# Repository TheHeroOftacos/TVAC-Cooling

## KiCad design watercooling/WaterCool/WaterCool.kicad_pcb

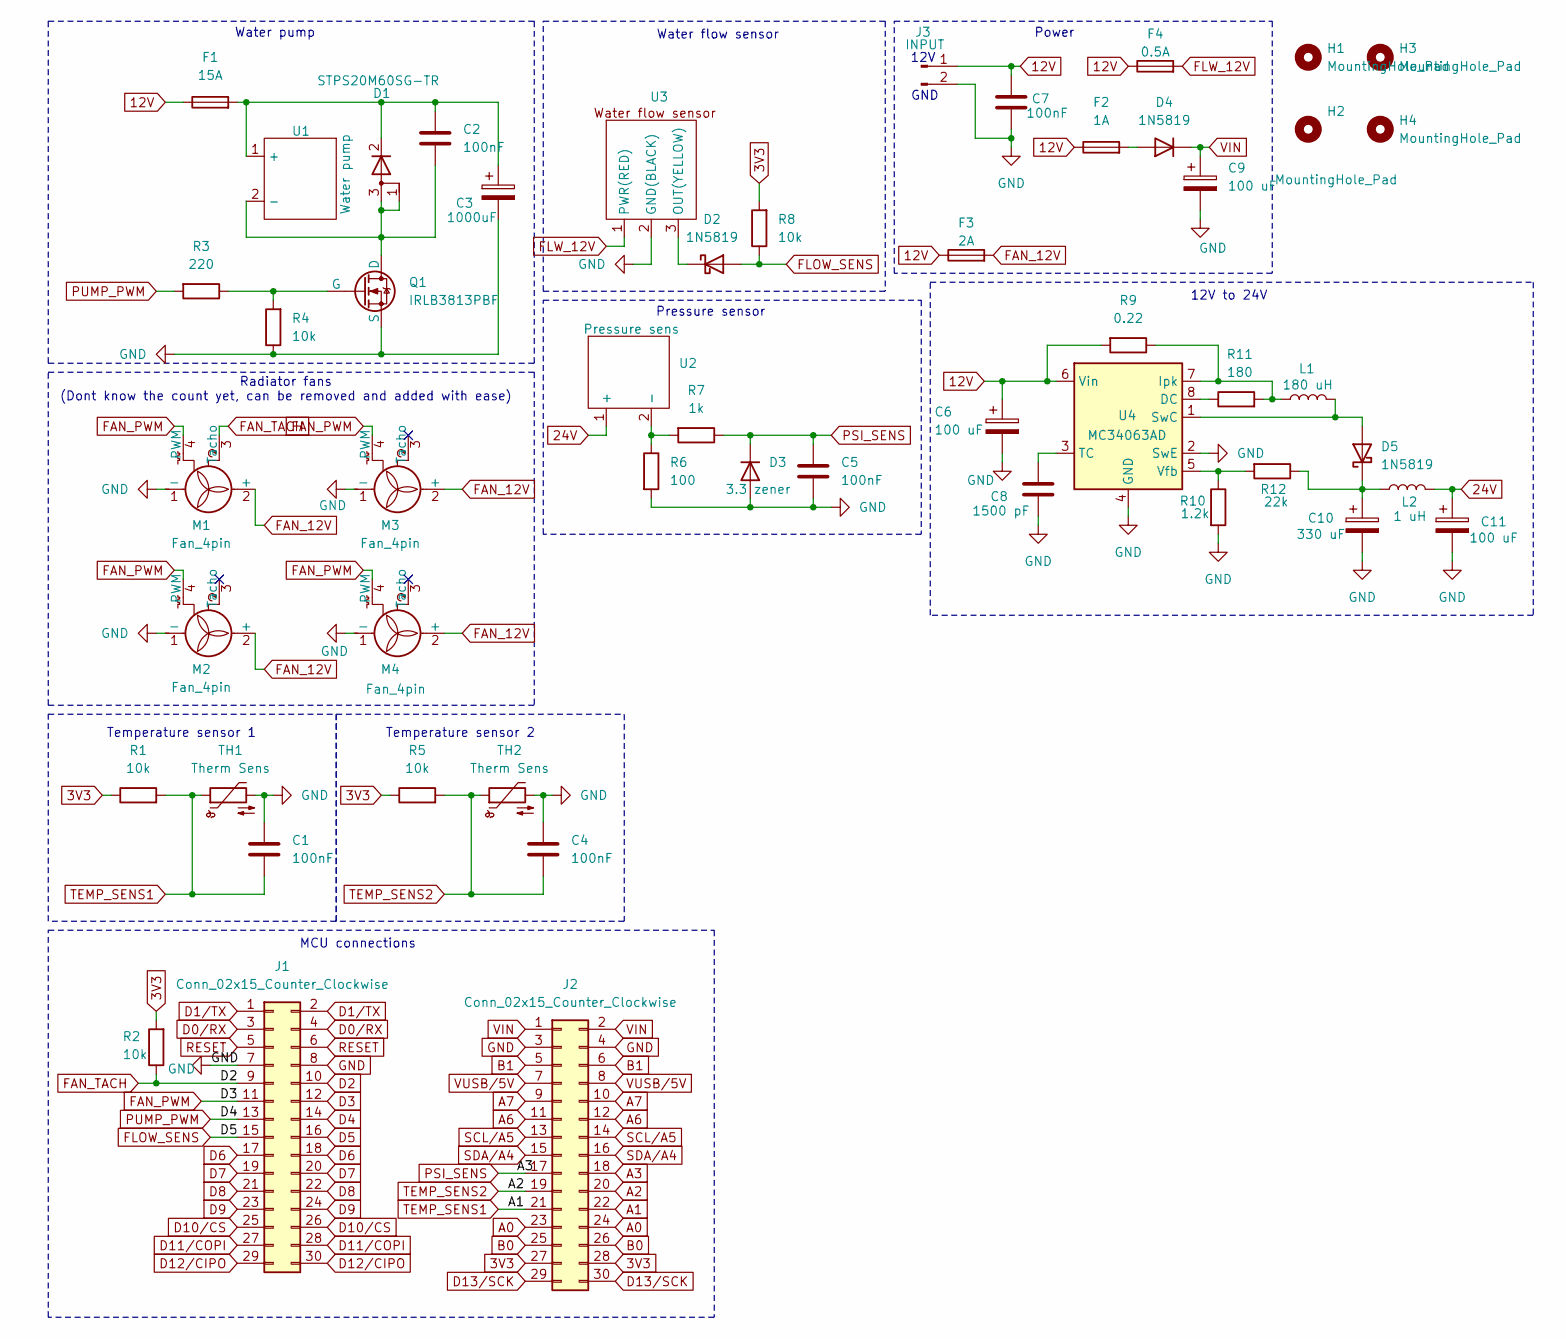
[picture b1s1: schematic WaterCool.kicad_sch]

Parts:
C1, C2, C4, C5, C7: 100nF; C_1210_3225Metric_Pad1.33x2.70mm_HandSolder
C3: 1000uF; CP_Elec_10x10.5
C6, C9, C11: 100 uF; CP_Elec_10x10.5
C8: 1500 pF; C_0805_2012Metric_Pad1.18x1.45mm_HandSolder
C10: 330 uF; CP_Elec_10x10.5
D1: STPS20M60SG-TR; TO-263-2
D2, D4, D5: 1N5819; D_SOD-123
D3: 3.3 zener; D_SOD-123
F1: 15A; Fuse_2512_6332Metric_Pad1.52x3.35mm_HandSolder
F2: 1A; Fuse_0805_2012Metric_Pad1.15x1.40mm_HandSolder
F3: 2A; Fuse_0805_2012Metric_Pad1.15x1.40mm_HandSolder
F4: 0.5A; Fuse_0805_2012Metric_Pad1.15x1.40mm_HandSolder
H1, H2, H3, H4: MountingHole_Pad; MountingHole_3.2mm_M3
J1, J2: Conn_02x15_Counter_Clockwise; PinSocket_2x15_P2.54mm_Vertical
J3: INPUT; AMASS_XT60-M_1x02_P7.20mm_Vertical
L1: 180 uH; L_Coilcraft_MSS1048-XXX
L2: 1 uH; L_Vishay_IHLP-1212
M1, M2, M3, M4: Fan_4pin; PinHeader_1x04_P2.54mm_Vertical
Q1: IRLB3813PBF; TO-220-3_Horizontal_TabDown
R1, R2, R4, R5, R8: 10k; R_0805_2012Metric_Pad1.20x1.40mm_HandSolder
R3: 220; R_0805_2012Metric_Pad1.20x1.40mm_HandSolder
R6: 100; R_0805_2012Metric_Pad1.20x1.40mm_HandSolder
R7: 1k; R_0805_2012Metric_Pad1.20x1.40mm_HandSolder
R9: 0.22; R_0805_2012Metric_Pad1.20x1.40mm_HandSolder
R10: 1.2k; R_0805_2012Metric_Pad1.20x1.40mm_HandSolder
R11: 180; R_0805_2012Metric_Pad1.20x1.40mm_HandSolder
R12: 22k; R_0805_2012Metric_Pad1.20x1.40mm_HandSolder
TH1, TH2: Therm Sens; JST_PH_S2B-PH-SM4-TB_1x02-1MP_P2.00mm_Horizontal
U1: Water pump; Wuerth_691311400102_P7.62mm
U2: Pressure sens; JST_PH_S2B-PH-SM4-TB_1x02-1MP_P2.00mm_Horizontal
U3: JST_PH_B3B-PH-K_1x03_P2.00mm_Vertical
U4: MC34063AD; SOIC-8_3.9x4.9mm_P1.27mm

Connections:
3V3: J2.27, J2.28, R1.1, R2.2, R5.1, R8.2
12V: C6.1, C7.1, F1.1, F2.1, F3.1, F4.1, J3.1, R9.2, U4.6 (Vin)
24V: C11.1, L2.2, U2.1 (+); also elsewhere on the board
A0: J2.23, J2.24
A1: C1.2, J2.21, J2.22, R1.2, TH1.1; also elsewhere on the board
A2: C4.2, J2.19, J2.20, R5.2, TH2.1; also elsewhere on the board
A3: C5.2, D3.1 (K), J2.17, J2.18, R7.1
A6: J2.11, J2.12
A7: J2.9, J2.10
B0: J2.25, J2.26
B1: J2.5, J2.6
D0/RX: J1.3, J1.4
D1/TX: J1.1, J1.2
D2: J1.9, J1.10, M1.3 (Tacho), R2.1
D3: J1.11, J1.12, M1.4 (PWM), M2.4 (PWM), M3.4 (PWM), M4.4 (PWM)
D4: J1.13, J1.14, R3.2
D5: D2.2 (A), J1.15, J1.16, R8.1
D6: J1.17, J1.18
D7: J1.19, J1.20
D8: J1.21, J1.22
D9: J1.23, J1.24
D10/CS: J1.25, J1.26
D11/COPI: J1.27, J1.28
D12/CIPO: J1.29, J1.30
D13/SCK: J2.29, J2.30
FAN_12V: F3.2, M1.2 (+), M2.2 (+), M3.2 (+), M4.2 (+)
FLW_12V: F4.2, U3.1 (PWR(RED))
GND: C1.1, C3.2, C4.1, C5.1, C6.2, C7.2, C8.1, C9.2, C10.2, C11.2, D3.2 (A), J1.7, J1.8, J2.3, J2.4, J3.2, M1.1 (-), M2.1 (-), M3.1 (-), M4.1 (-), Q1.3 (S), R4.1, R6.2, R10.2, TH1.2, TH2.2, U3.2 (GND(BLACK)), U4.2 (SwE), U4.4 (GND); also elsewhere on the board
unnamed: C2.1, C3.1, D1.2 (K), F1.2, U1.1 (+)
unnamed: D2.1 (K), U3.3 (OUT(YELLOW))
unnamed: D4.2 (A), F2.2
unnamed: D5.2 (A), L1.2, U4.1 (SwC)
unnamed: C10.1, D5.1 (K), L2.1, R12.1
unnamed: C2.2, D1.1 (A), D1.3 (A), Q1.1 (D), U1.2 (-)
unnamed: Q1.2 (G), R3.1, R4.2
unnamed 35: R6.1, R7.2, U2.2 (-); also elsewhere on the board
unnamed: R11.1, U4.8 (DC)
unnamed: L1.1, R9.1, R11.2, U4.7 (Ipk)
unnamed: C8.2, U4.3 (TC)
unnamed: R10.1, R12.2, U4.5 (Vfb)
RESET: J1.5, J1.6
SCL/A5: J2.13, J2.14
SDA/A4: J2.15, J2.16
VIN: C9.1, D4.1 (K), J2.1, J2.2
VUSB/5V: J2.7, J2.8

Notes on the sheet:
Temperature sensor 2
GND
Temperature sensor 1
MCU connections
Pressure sensor
Water flow sensor
12V
Water pump
12V to 24V
Power
Radiator fans (Dont know the count yet, can be removed and added with ease)

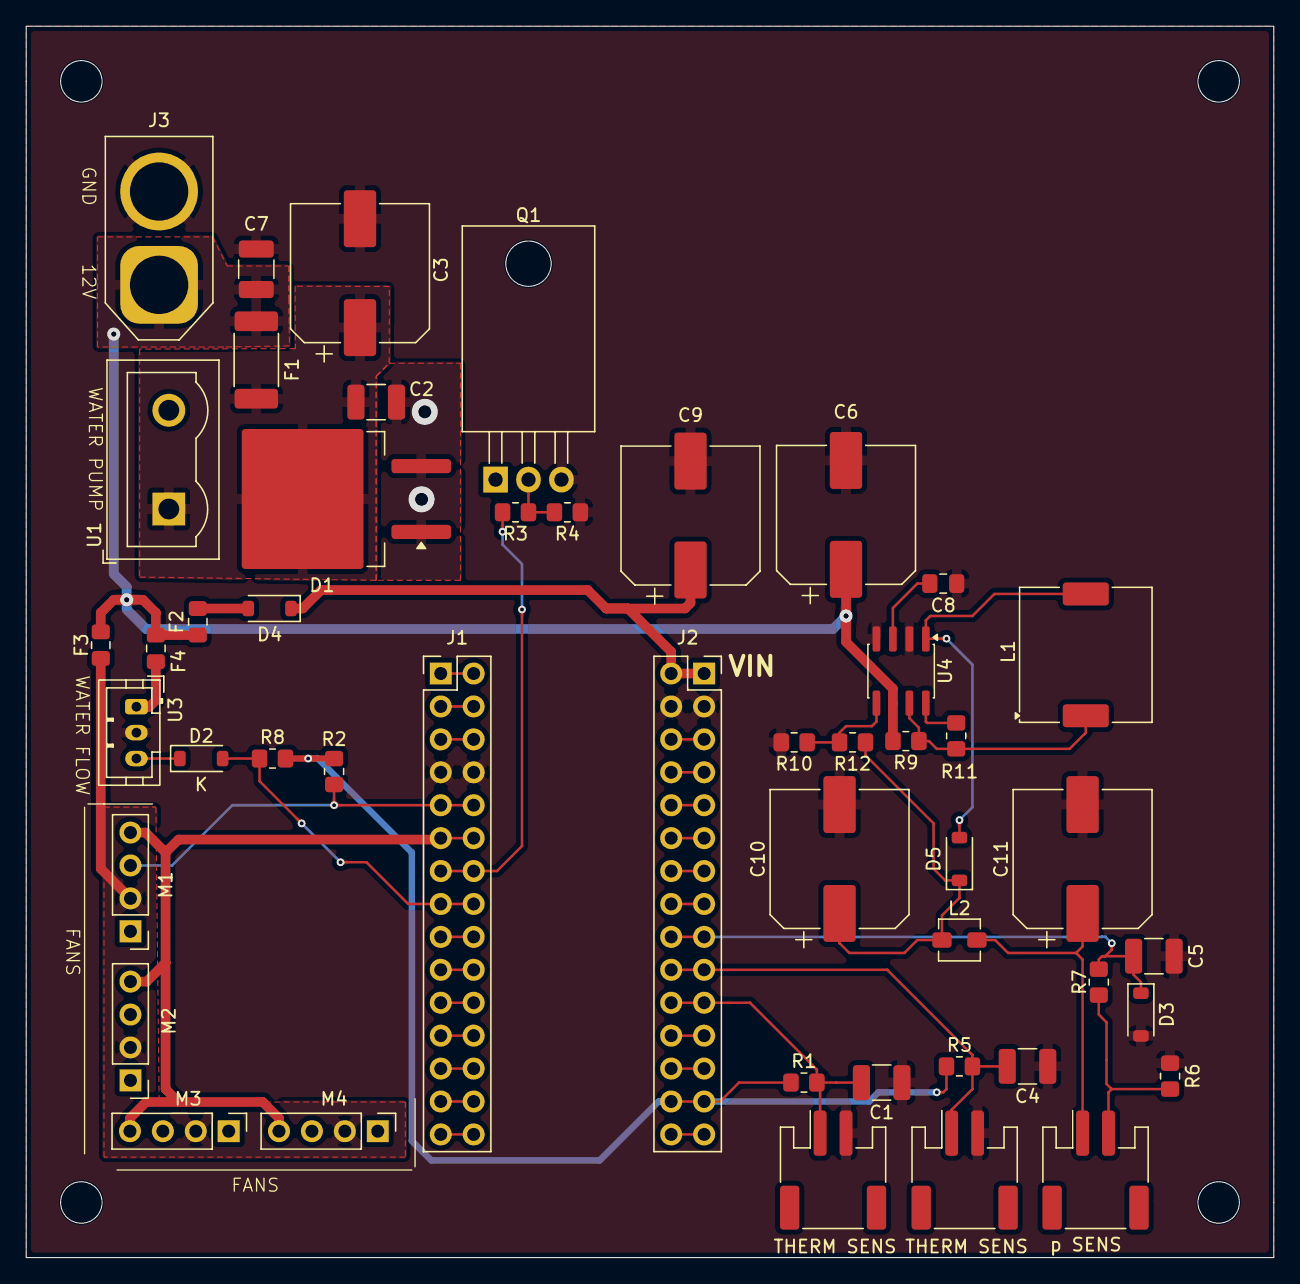
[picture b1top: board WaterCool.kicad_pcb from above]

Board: 2 copper layers, 96.2 x 95.0 mm, 52 parts (0 on the bottom side), 45 nets.

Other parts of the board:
THERM SENS: Therm Sens; JST_PH_S2B-PH-SM4-TB_1x02-1MP_P2.00mm_Horizontal
THERM SENS#2: Therm Sens; JST_PH_S2B-PH-SM4-TB_1x02-1MP_P2.00mm_Horizontal
p SENS: Pressure sens; JST_PH_S2B-PH-SM4-TB_1x02-1MP_P2.00mm_Horizontal

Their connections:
24V: p SENS.1 (+); also elsewhere on the board
A1: THERM SENS#2.1; also elsewhere on the board
A2: THERM SENS.1; also elsewhere on the board
GND: THERM SENS.2, THERM SENS#2.2; also elsewhere on the board
unnamed 35: p SENS.2 (-); also elsewhere on the board
